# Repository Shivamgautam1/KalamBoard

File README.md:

# KalamBoard
Open Source ATmega328 based Dev board with onboard Sensors, Relays &amp; Motor Drivers

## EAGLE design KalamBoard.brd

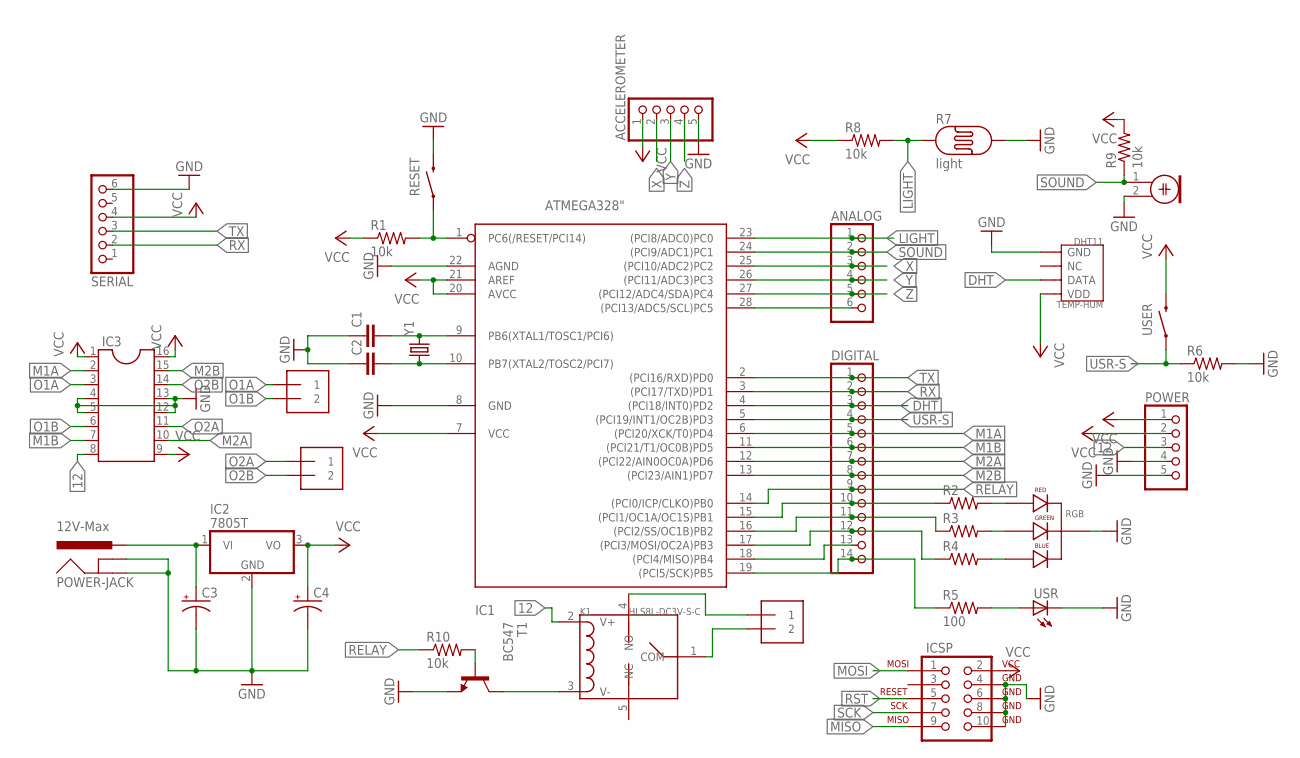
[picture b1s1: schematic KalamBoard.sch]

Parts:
ACCELEROMETER: PINHD-1X5; 1X05
ANALOG: PINHD-1X6; 1X06
C1, C2: 0.1UF-50V-20%(PTH)KIT-EZ; CAP-PTH-SMALL-KIT
C3, C4: 10UF-25V-20%(PTH); CPOL-RADIAL-10UF-25V
DIGITAL: PINHD-1X14; 1X14
IC1: ATMEGA328"; ATMEGA328
IC2: 7805T; TO220H
IC3: DIL16S; SOCKET-16
ICSP: AVR_SPI_PROG2PTH; AVR_ICSP
K1: HLS8L-DC3V-S-C; REY5-19.0X15.0X15.0MM
MOTOR1, MOTOR2: 1X2-3.5MM
POWER: PINHD-1X5; 1X05
POWER-JACK: 12V-Max; POWER_JACK
R1, R6, R8, R9, R10: 10k; RESISTOR
R2, R3, R4: RESISTOR1/6WATT; RESISTOR
R5: 100; RESISTOR
R7: light; PHOTOCELL
RELAY: 1X2-3.5MM
RESET: MOMENTARY_SWITCH"; MOMENTARY_SWITCH
RGB: LED-RGB-CC-THRUDIFFUSE; LED-RGB-THRU
SERIAL: PINHD-1X6; 1X06
SOUND: ELECTRET_MICROPHON-F6050AP; F6050AP
T1: BC547; TO92
TEMP-HUM: DHT11; SNR4-2.54-15.5X12.0X5.5MM
USER: MOMENTARY_SWITCH"; MOMENTARY_SWITCH
USR: LED3MM; LED
Y1: CRYSTALHC49US; HC49US

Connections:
12: C3.1 (+), IC2.1 (VI), IC3.8, K1.2 (V+), POWER.3, POWER-JACK.PWR
DHT: DIGITAL.3, IC1.4 ((PCI18/INT0)PD2), TEMP-HUM.2 (DATA)
GND: ACCELEROMETER.5, C1.1, C2.1, C3.2 (-), C4.2 (-), IC1.8 (GND), IC1.22 (AGND), IC2.2 (GND), IC3.4, IC3.5, IC3.12, IC3.13, ICSP.4 (GND), ICSP.6 (GND), ICSP.8 (GND), ICSP.10 (GND), POWER.4, POWER.5, POWER-JACK.GND, POWER-JACK.GNDBREAK, R6.2, R7.2, RESET.3 (2), RGB.2 (CATHODE), SERIAL.6, SOUND.2, T1.1 (E), TEMP-HUM.4 (GND), USR.K (C)
LIGHT: ANALOG.1, IC1.23 ((PCI8/ADC0)PC0), R7.1, R8.2
M1A: DIGITAL.5, IC1.6 ((PCI20/XCK/T0)PD4), IC3.2
M1B: DIGITAL.6, IC1.11 ((PCI21/T1/OC0B)PD5), IC3.7
M2A: DIGITAL.7, IC1.12 ((PCI22/AIN0OC0A)PD6), IC3.10
M2B: DIGITAL.8, IC1.13 ((PCI23/AIN1)PD7), IC3.15
MISO: DIGITAL.13, IC1.18 ((PCI4/MISO)PB4), ICSP.9 (MISO)
MOSI: DIGITAL.12, IC1.17 ((PCI3/MOSI/OC2A)PB3), ICSP.1 (MOSI), R4.1
unnamed: C1.2, IC1.9 (PB6(XTAL1/TOSC1/PCI6)), Y1.2
unnamed: C2.2, IC1.10 (PB7(XTAL2/TOSC2/PCI7)), Y1.1
unnamed: R10.2, T1.2 (B)
unnamed: K1.3 (V-), T1.3 (C)
unnamed: K1.4 (NO), RELAY.1
unnamed: ANALOG.6, IC1.28 ((PCI13/ADC5/SCL)PC5)
unnamed: K1.1 (COM), RELAY.2
unnamed: DIGITAL.10, IC1.15 ((PCI1/OC1A/OC1S)PB1), R2.1
unnamed: DIGITAL.11, IC1.16 ((PCI2/SS/OC1B)PB2), R3.1
unnamed: R2.2, RGB.1 (RED_CATHODE)
unnamed: R3.2, RGB.3 (GREEN_CATHODE)
unnamed: R4.2, RGB.4 (BLUE_CATHODE)
unnamed: R5.2, USR.A
O1A: IC3.3, MOTOR1.1
O1B: IC3.6, MOTOR1.2
O2A: IC3.11, MOTOR2.1
O2B: IC3.14, MOTOR2.2
RELAY: DIGITAL.9, IC1.14 ((PCI0/ICP/CLKO)PB0), R10.1
RST: IC1.1 (PC6(/RESET/PCI14)), ICSP.5 (RESET), R1.2, RESET.1
RX: DIGITAL.2, IC1.3 ((PCI17/TXD)PD1), SERIAL.2
SCK: DIGITAL.14, IC1.19 ((PCI5/SCK)PB5), ICSP.7 (SCK), R5.1
SOUND: ANALOG.2, IC1.24 ((PCI9/ADC1)PC1), R9.1, SOUND.1
TX: DIGITAL.1, IC1.2 ((PCI16/RXD)PD0), SERIAL.3
USR-S: DIGITAL.4, IC1.5 ((PCI19/INT1/OC2B)PD3), R6.1, USER.1
VCC: ACCELEROMETER.1, C4.1 (+), IC1.7 (VCC), IC1.20 (AVCC), IC1.21 (AREF), IC2.3 (VO), IC3.1, IC3.9, IC3.16, ICSP.2 (VCC), POWER.1, POWER.2, R1.1, R8.1, R9.2, SERIAL.4, TEMP-HUM.1 (VDD), USER.3 (2)
X: ACCELEROMETER.2, ANALOG.3, IC1.25 ((PCI10/ADC2)PC2)
Y: ACCELEROMETER.3, ANALOG.4, IC1.26 ((PCI11/ADC3)PC3)
Z: ACCELEROMETER.4, ANALOG.5, IC1.27 ((PCI12/ADC4/SDA)PC4)

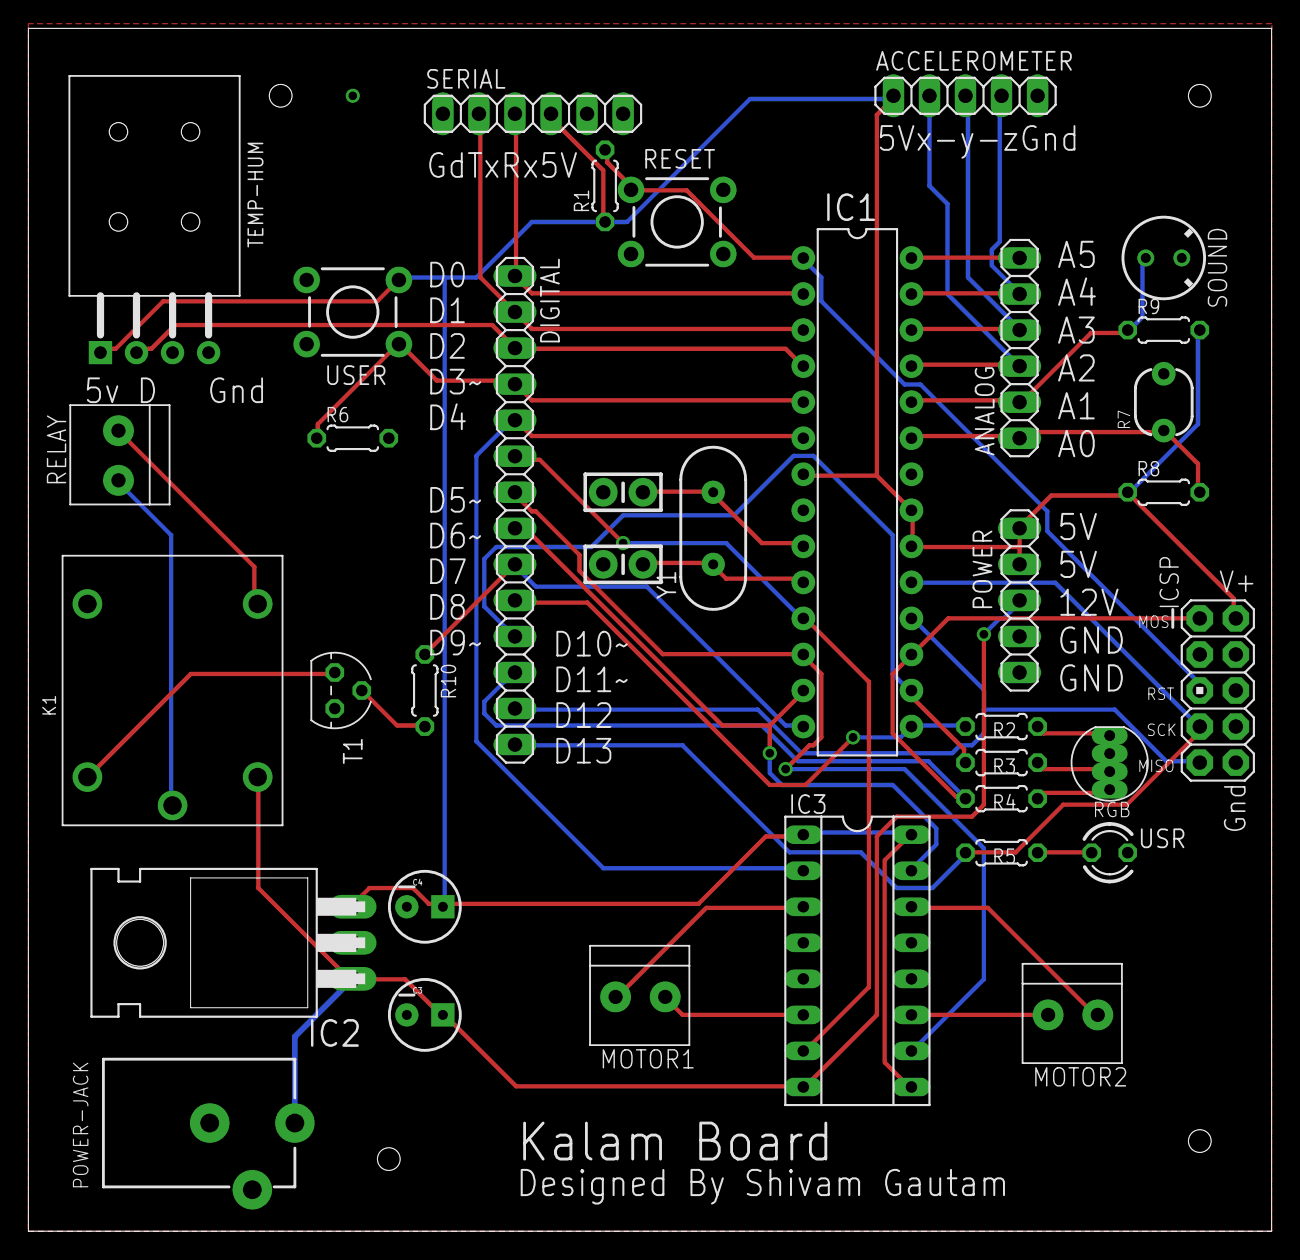
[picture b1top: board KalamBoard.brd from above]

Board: 2 copper layers, 87.6 x 84.8 mm, 36 parts (0 on the bottom side), 38 nets.

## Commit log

2017-06-07 Gerber Files for Fabrication
2017-06-07 Eagle Files

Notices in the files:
parts and their libraries:
SparkFun-Capacitors: Licensing: Creative Commons ShareAlike 4.0 International - https://creativecommons.org/licenses/by-sa/4.0
